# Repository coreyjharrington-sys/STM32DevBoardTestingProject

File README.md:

# STM32Devboard – Firmware + HITL Simulation in CI

*A combined hardware + firmware + automated test demonstration project*

This project demonstrates a **Hardware-In-The-Loop (HITL)-style automated test pipeline** using a **custom STM32F103C8T6 development board that I designed in KiCad**, combined with firmware validation using **Pytest** and **GitHub Actions**.

When code is pushed or a pull request is opened, the CI workflow automatically:

1. **Builds the firmware**
2. **Flashes the STM32F103C8T6 board** connected to the GitHub Actions runner
3. **Runs Pytest-based functional tests** against the physical device
4. **Reports pass/fail status** back to GitHub

This pipeline simulates a professional HITL test system, showing how real hardware can be validated automatically using continuous integration.

---

## 📦 Project Structure

```
Test_Serial/
│
├── firmware/              # Embedded C firmware for STM32F103C8T6
│   ├── src/
│   ├── include/
│   └── (build artifacts ignored via .gitignore)
│
├── tests/                 # Pytest functional tests for HITL validation
│   ├── test_commands.py
│   ├── test_math_ops.py
│   ├── dut_config.json    # PID/VID → auto-detect COM port
│   └── helpers/
│
├── hardware/              # Full KiCad project for the custom STM32 board
│   ├── *.kicad_pro
│   ├── *.kicad_sch
│   ├── *.kicad_pcb
│   ├── symbols/
│   └── footprints/
│
├── scripts/               # Optional Python helper scripts
│
├── requirements.txt       # Python dependencies for Pytest HITL tests
├── .gitignore
└── README.md
```

The KiCad project is intentionally included to showcase the board design to recruiters/employers.
Only temporary, generated, and fabrication files are ignored via `.gitignore`.

---

## 🔧 Hardware Overview (Custom STM32F103C8T6 Board)

The DUT is a custom development board designed in **KiCad**. The design includes:

* STM32F103C8T6 microcontroller
* USB-to-UART for firmware testing
* SWD debug header
* Power regulation and filtering
* Breakouts for serial, GPIO, and test pins

The PCB and schematic files are included so reviewers can inspect routing, component selection, layout style, and design organization.

This hardware is used directly in the HITL CI workflow.

Note: If you wish to run this demo yourself a Blue Pill Developement board can be sustituted.

Note: Credit to Phil's Lab for board design tutorial
https://www.youtube.com/watch?v=aVUqaB0IMh4

---

## 🧩 Firmware Overview

The embedded firmware is intentionally minimal and built for testing.
It implements a UART command interface supporting:

* A **command/response** handshake
* Four arithmetic operations:

  * **Add**
  * **Subtract**
  * **Multiply**
  * **Divide**
* A small set of additional commands used by the test suite

This makes the board ideal for CI-driven firmware verification.

Note: If running this demo use ST-LINK V2 Programmer for flashing the board.

---

📦 Dependencies
🛠 Development Dependencies
These are tools used during development and design, not required on the CI runner itself:
- STM32CubeMX → generates firmware scaffolding, peripheral initialization code, and startup files for the STM32F103C8T6
- KiCad → full PCB and schematic design for the custom STM32 development board

---

🖥️ Runner Dependencies
These must be installed and available on the self‑hosted runner before the HITL workflow can execute:
- Docker → builds STM32 firmware inside a reproducible container
- STM32CubeProgrammer CLI (CubeProgrammerCLI) → flashes firmware to the STM32 board via SWD
- Python 3.x → interpreter for running HITL test suites
- Conda → environment manager for reproducible Python dependencies
- Git → required by actions/checkout to pull the repository
✅ Verification Checklist
Run these commands on the runner to confirm installation:
docker --version
CubeProgrammerCLI --version
python --version
conda --version
git --version

All commands should return valid version information. If any fail, install or update the missing dependency before running the workflow

---

🐍 Python Dependencies (via Conda)
The Python environment is defined in environment.yml and updated in CI with:
conda env update --file environment.yml --name testframework --prune

Key libraries include:
- pytest → functional test framework for HITL validation
- pyserial → serial communication with the STM32 board
- utility modules → logging, JSON parsing, device enumeration, and test orchestration

---

## 🧪 HITL Test Flow (Pytest)

After flashing the firmware, GitHub Actions triggers **Pytest** to validate real hardware behavior:

* A Python script scans the system’s USB devices
* It loads the `dut_config.json` file to locate the board based on:

  * **PID**
  * **VID**
  * **Baudrate**
* The test suite opens the serial port and sends each supported command
* Responses are parsed and validated

Example Pytest coverage:

* Handshake / ping test
* Add / subtract / multiply / divide
* Error format tests
* Command framing validation

Test artifacts (logs, HTML output, temp files) are fully ignored via `.gitignore`.

---

## 🐳 Dockerized Firmware Build

A Docker container is provided for **reproducible STM32F103 firmware builds**. It includes the ARM toolchain and necessary libraries.

### Usage

Build the Docker image once:

```bash
docker build -t stm32devboardcompiler .
```

Compile firmware from your local source by mounting the repo:

```bash
docker run --rm -v ${PWD}:/workspace -w /workspace/firmware stm32devboardcompiler make all
```

To clean and rebuild:

```bash
docker run --rm -v ${PWD}:/workspace -w /workspace/firmware stm32devboardcompiler make clean all
```

**Notes:**

* The container is purely for building firmware; Python HITL tests run on the host to access the physical board.
* Source code and Makefile remain on the host, so edits are immediately reflected in builds.

---

## ⚙️ GitHub Actions CI

Our CI/CD pipeline is defined in `.github/workflows/*.yml` files using GitHub Actions syntax.  
Each workflow specifies **triggers** under the `on:` key and **jobs** under the `jobs:` key.

### 🔔 Triggers
The workflow runs automatically on:
- **Push** → any branch pushed to the remote repo
- **Pull request** → PRs targeting `main`
- **workflow_dispatch** → manual trigger from the Actions tab

### 🛠 Workflow steps
The hitl-test job runs on a self‑hosted runner (with STM32 hardware attached) and performs:
- Checkout repo – pulls the latest code
- Ensure Docker – verifies Docker is installed
- Build firmware – compiles with Dockerized ARM toolchain (make clean all)
- Check CubeProgrammerCLI – verifies ST’s programmer tool is available on the runner
- Flash firmware – programs the STM32F103C8T6 via CubeProgrammerCLI
- Verify Python & Conda – ensures Python and Conda are available
- Update Conda environment – applies environment.yml to the testframework environment (with pruning)
- Run HITL tests – activates the Conda environment and executes pytest against the physical device
🔄 Feedback loop
This setup provides a fully automated feedback loop:
- Firmware is built and flashed
- Hardware‑in‑the‑loop tests validate behavior
- Results are collected and surfaced directly in GitHub

### 🔄 Feedback loop
This setup provides a **fully automated feedback loop**:
- Firmware is built and flashed
- Hardware‑in‑the‑loop tests validate behavior
- Results are collected and surfaced directly in GitHub

---

## 🐍 Python Environment

🐍 Python Environment
This CI workflow uses Conda to manage dependencies reproducibly.

Update the environment locally with:
conda env update --file environment.yml --name testframework --prune

Activate the environment:
conda activate testframework

Run tests:
python -m pytest --maxfail=1 --disable-warnings -q

Key libraries include:
- pytest
- pyserial
- Utility modules for device enumeration and communications

---

## 🔌 DUT Configuration File (`dut_config.json`)

This file determines which device to test against:

```json
{
    "pid": "0x1234",
    "vid": "0x5678",
    "baudrate": 115200
}
```

Pytest uses these identifiers to automatically determine the correct COM port.

This avoids any hard-coding and ensures the CI system always targets the correct board.

---

## 📝 License

This project is licensed under the **MIT General Public License (GPL)**.
See the `LICENSE` file for details.

---

## 🛠️ Future Improvements

* SQL logging of test metrics
* More extensive command set
* Automated hardware reset between test cycles
* Multi-device testing support
* Hardware fault injection
* Coverage reporting and test data visualization
* Linting and SCA of Embedded Code
* Add I2C and UART communcation
* Add automated testing with logic analyzer
* ccache in Docker for faster builds

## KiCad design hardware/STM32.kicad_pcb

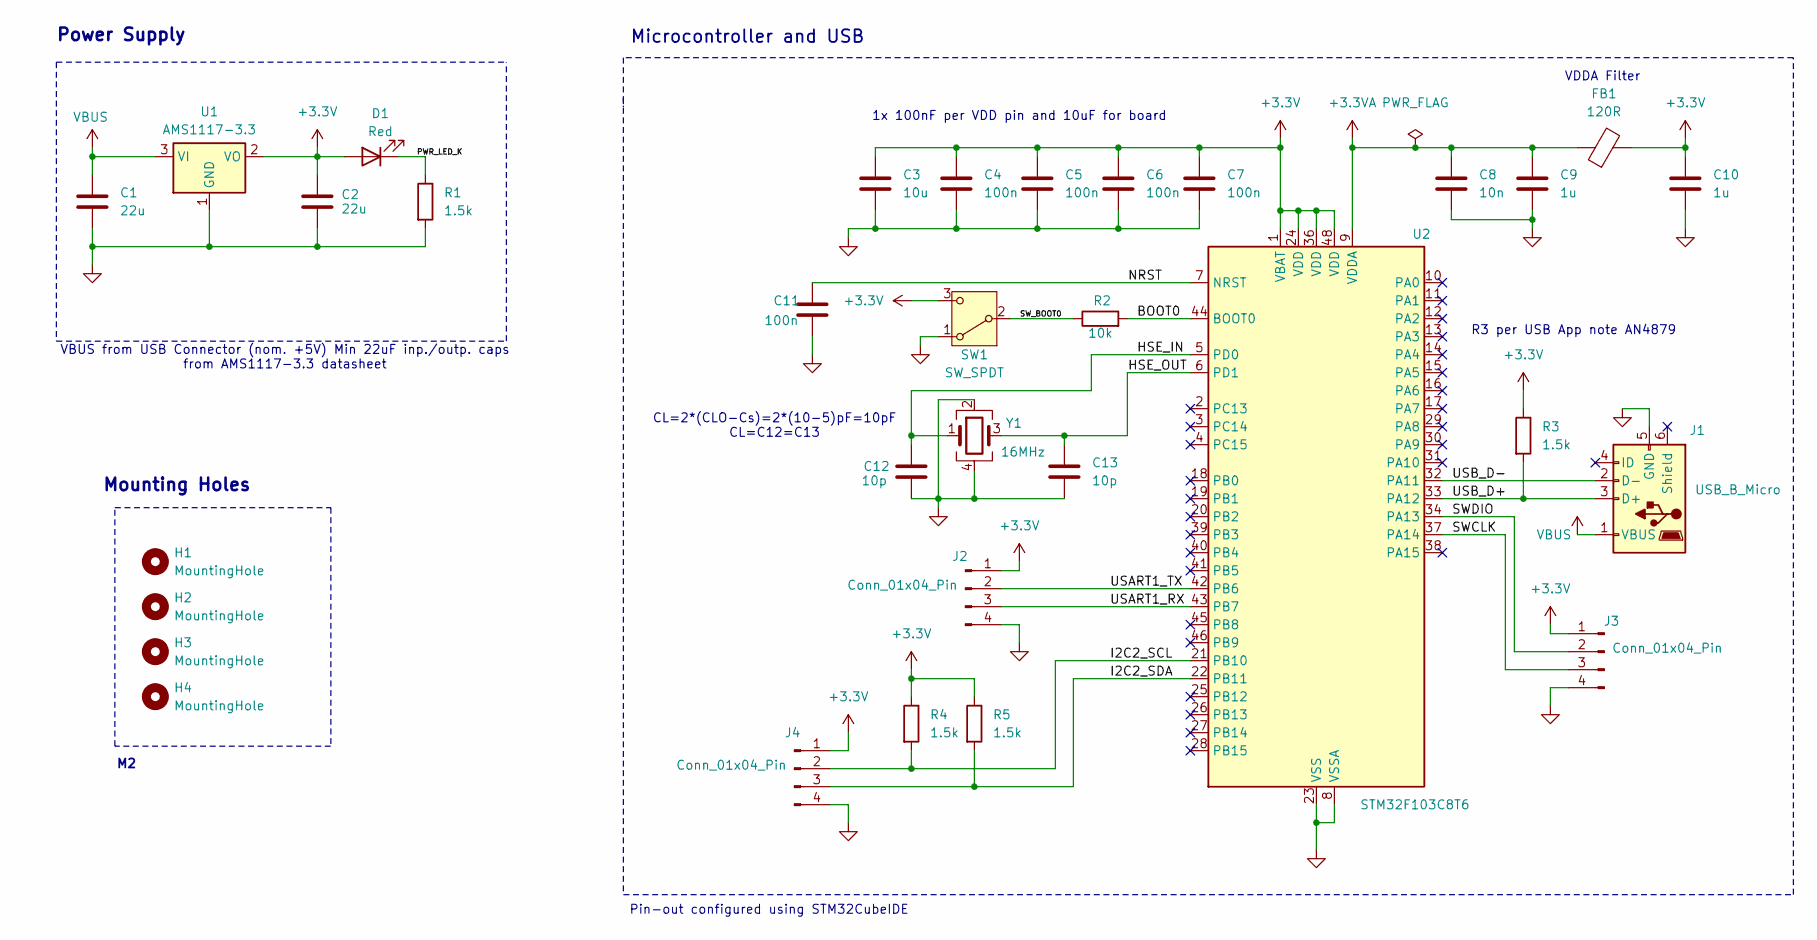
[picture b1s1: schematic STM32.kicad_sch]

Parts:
C1, C2: 22u; C_0805_2012Metric
C3: 10u; C_0603_1608Metric
C4, C5, C6, C7, C11: 100n; C_0402_1005Metric
C8: 10n; C_0402_1005Metric
C9, C10: 1u; C_0402_1005Metric
C12, C13: 10p; C_0402_1005Metric
D1: Red; LED_0603_1608Metric
FB1: 120R; L_0603_1608Metric
H1, H2, H3, H4: MountingHole; MountingHole_2.2mm_M2
J1: USB_B_Micro; USB_Micro-B_Wuerth_629105150521
J2, J3, J4: Conn_01x04_Pin; PinHeader_1x04_P2.54mm_Vertical
R1, R3, R4, R5: 1.5k; R_0402_1005Metric
R2: 10k; R_0402_1005Metric
SW1: SW_SPDT; SW_SPDT_PCM12
U1: AMS1117-3.3; SOT-223-3_TabPin2
U2: STM32F103C8T6; LQFP-48_7x7mm_P0.5mm
Y1: 16MHz; Crystal_SMD_3225-4Pin_3.2x2.5mm

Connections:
+3.3V: C2.1, C3.1, C4.1, C5.1, C6.1, C7.1, C10.1, D1.2 (A), FB1.2, J2.1, J3.1, J4.1, R3.1, R4.1, R5.1, SW1.3 (C), U1.2 (VO), U2.1 (VBAT), U2.24 (VDD), U2.36 (VDD), U2.48 (VDD)
+3.3VA: C8.1, C9.1, FB1.1, U2.9 (VDDA)
/BOOT0: R2.2, U2.44 (BOOT0)
/HSE_IN: C12.1, U2.5 (PD0), Y1.1
/HSE_OUT: C13.1, U2.6 (PD1), Y1.3
/I2C2_SCL: J4.2, R4.2, U2.21 (PB10)
/I2C2_SDA: J4.3, R5.2, U2.22 (PB11)
/NRST: C11.1, U2.7 (NRST)
/PWR_LED_K: D1.1 (K), R1.1
/SWCLK: J3.3, U2.37 (PA14)
/SWDIO: J3.2, U2.34 (PA13)
/SW_BOOT0: R2.1, SW1.2 (B)
/USART1_RX: J2.3, U2.43 (PB7)
/USART1_TX: J2.2, U2.42 (PB6)
/USB_D+: J1.3 (D+), R3.2, U2.33 (PA12)
/USB_D-: J1.2 (D-), U2.32 (PA11)
GND: C1.2, C2.2, C3.2, C4.2, C5.2, C6.2, C7.2, C8.2, C9.2, C10.2, C11.2, C12.2, C13.2, J1.5 (GND), J1.6 (Shield), J2.4, J3.4, J4.4, R1.2, SW1.1 (A), U1.1 (GND), U2.8 (VSSA), U2.23 (VSS), U2.35 (VSS), U2.47 (VSS), Y1.2, Y1.4
VBUS: C1.1, J1.1 (VBUS), U1.3 (VI)

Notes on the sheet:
VDDA Filter
Pin-out configured using STM32CubeIDE
1x 100nF per VDD pin and 10uF for board
CL=2*(CLO-Cs)=2*(10-5)pF=10pF CL=C12=C13
Microcontroller and USB
VBUS from USB Connector (nom. +5V) Min 22uF inp./outp. caps from AMS1117-3.3 datasheet
R3 per USB App note AN4879
Power Supply
Mounting Holes

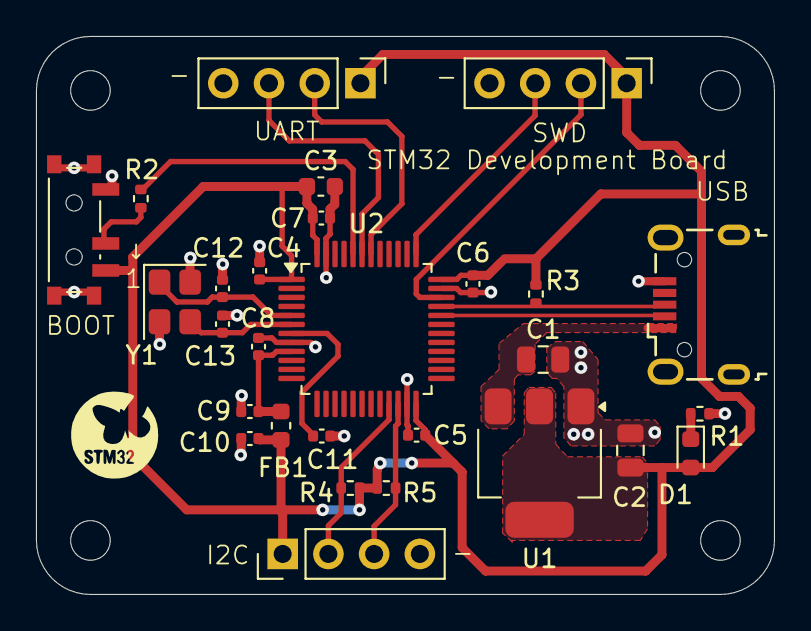
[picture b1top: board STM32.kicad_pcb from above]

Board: 2 copper layers, 41.0 x 31.0 mm, 32 parts (0 on the bottom side), 18 nets.

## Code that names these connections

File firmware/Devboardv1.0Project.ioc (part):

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Mcu.Name=STM32F103C(8-B)Tx
Mcu.Package=LQFP48
Mcu.UserName=STM32F103C8Tx
PA11.Mode=Device
PA11.Signal=USB_DM
PA12.Mode=Device
PA12.Signal=USB_DP
PA13.Mode=Serial_Wire
PA13.Signal=SYS_JTMS-SWDIO
PA14.Mode=Serial_Wire
PA14.Signal=SYS_JTCK-SWCLK
PD0-OSC_IN.Mode=HSE-External-Oscillator
PD0-OSC_IN.Signal=RCC_OSC_IN
PD1-OSC_OUT.Mode=HSE-External-Oscillator
PD1-OSC_OUT.Signal=RCC_OSC_OUT
RCC.HSEDivPLL=RCC_HSE_PREDIV_DIV2
RCC.HSE_VALUE=16000000
RCC.SYSCLKFreq_VALUE=72000000
RCC.SYSCLKSource=RCC_SYSCLKSOURCE_PLLCLK
board=custom

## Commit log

2025-11-30 Inital commit of STM32DevBoard project
2025-12-01 Added Dockerfile for compilation
2025-12-01 Added .dockerignore, and content to .gitignore and README.md
2025-12-01 added serial mock and markers
2025-12-01 Adding Github Actions workflow
2025-12-01 Updated HITLtest.yml to use conda instead of pip and reordered actions
2025-12-01 Updated HITLtest.yml to use PS instead of bash
2025-12-01 fixed issue with STM32_programmer call
2025-12-01 Added missing memory address for flash
2025-12-01 Fixed issue with backtick in HITLtest.yml
2025-12-01 added wrapping file path and explict type for address
2025-12-01 add absolute path for firmware binary and checks if binary exsists
2025-12-01 going back to last working program command
2025-12-02 adding pictures
2025-12-02 added workflow pic
2025-12-02 added workflow pic 2
2025-12-02 added workflow pic 3
2025-12-02 added workflow pic 4
2025-12-02 addedpauseforreconnect
2025-12-03 addTestResultsReport
2025-12-03 updatedActionsUploadv4
2025-12-03 firmwareOnly
2025-12-03 removedcomments
2025-12-03 removebacktick
2025-12-03 dockerimagechange
2025-12-03 changedDockerfile
2025-12-03 addedPicturesEditReadme
2025-12-04 addedJenkinsfile
2025-12-04 removed triggers
2025-12-04 PSinJenkins
2025-12-04 ChangedPausetoWaitState
2025-12-08 addedBinaryArtifact
